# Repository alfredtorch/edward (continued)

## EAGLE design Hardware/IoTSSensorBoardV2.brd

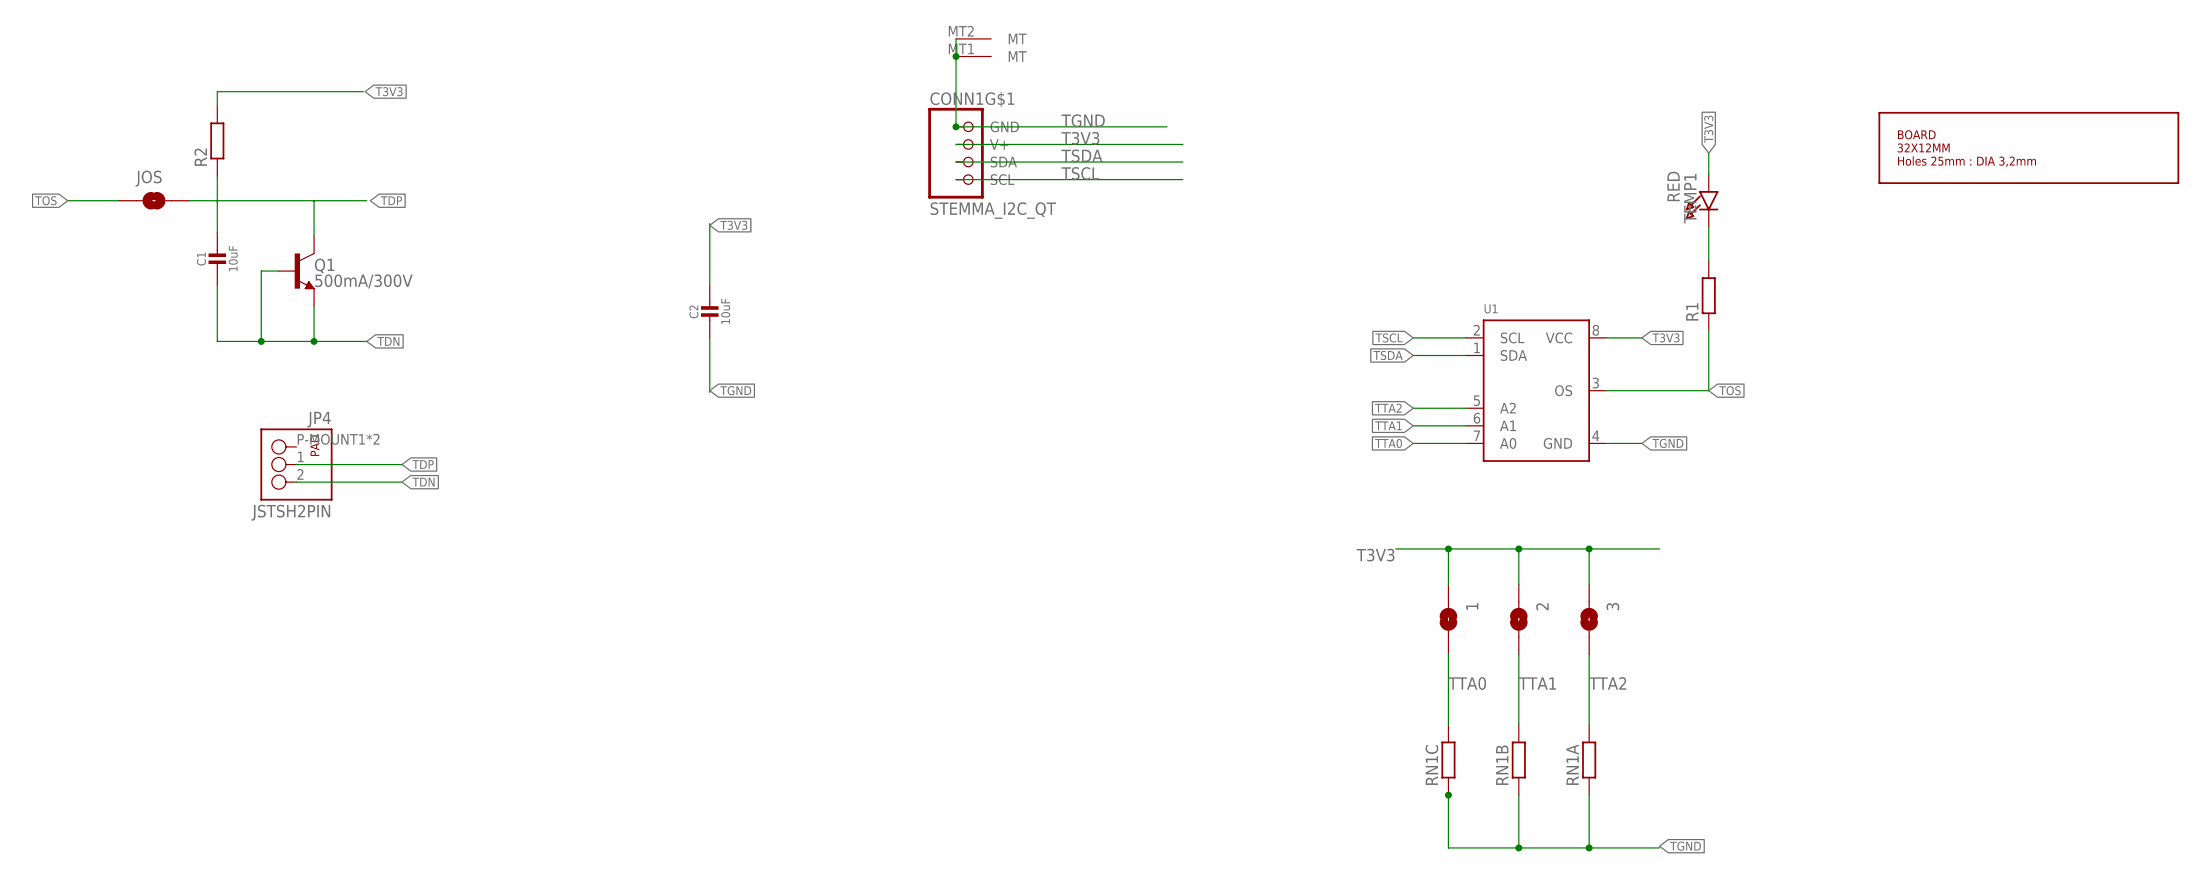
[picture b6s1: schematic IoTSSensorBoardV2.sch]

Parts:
1, 2, 3: JUMPER-SMT_2_NO_SILK; SMT-JUMPER_2_NO_SILK
C1, C2: 10uF; 0805-NO
CONN1: STEMMA_I2C_QT; JST_SH4
JOS: JUMPER-SMT_2_NO_SILK; SMT-JUMPER_2_NO_SILK
JP4: JSTSH2PIN; SM02B-SRSS-TB
Q1: 500mA/300V; SOT23-3
R1, R2: RESISTORR805-0805; R805
RN1: RESISTOR_ARRAY_4; RN8P-4R-CRA06S
TEMP1: RED; CHIPLED_0805
U1: TEMP_LM75B; TSSOP8
U$12: BOARD32X12; OVAL3212MM

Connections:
unnamed: R1.2, TEMP1.C
T3V3: 1.1, 2.1, 3.1, C2.1, CONN1.2 (V+), R2.2, TEMP1.A, U1.8 (VCC)
TDN: C1.2, JP4.2, Q1.1 (B), Q1.2 (E)
TDP: C1.1, JOS.2, JP4.1, Q1.3 (C), R2.1
TGND: C2.2, CONN1.1 (GND), CONN1.MT1 (MT), CONN1.MT2 (MT), RN1.1, RN1.2 (1), RN1.3 (1), U1.4 (GND)
TOS: JOS.1, R1.1, U1.3 (OS)
TSCL: CONN1.4 (SCL), U1.2 (SCL)
TSDA: CONN1.3 (SDA), U1.1 (SDA)
TTA0: 1.2, RN1.6 (2), U1.7 (A0)
TTA1: 2.2, RN1.7 (2), U1.6 (A1)
TTA2: 3.2, RN1.8 (2), U1.5 (A2)

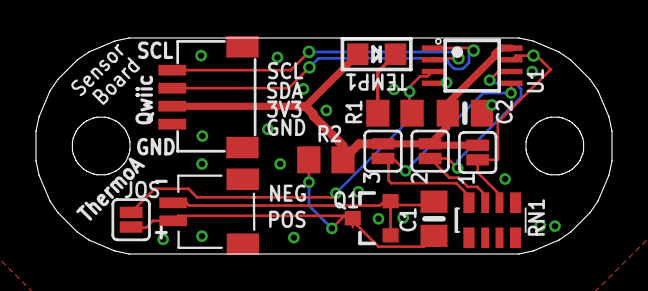
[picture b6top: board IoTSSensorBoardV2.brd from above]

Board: 2 copper layers, 32.0 x 12.0 mm, 15 parts (0 on the bottom side), 11 nets.

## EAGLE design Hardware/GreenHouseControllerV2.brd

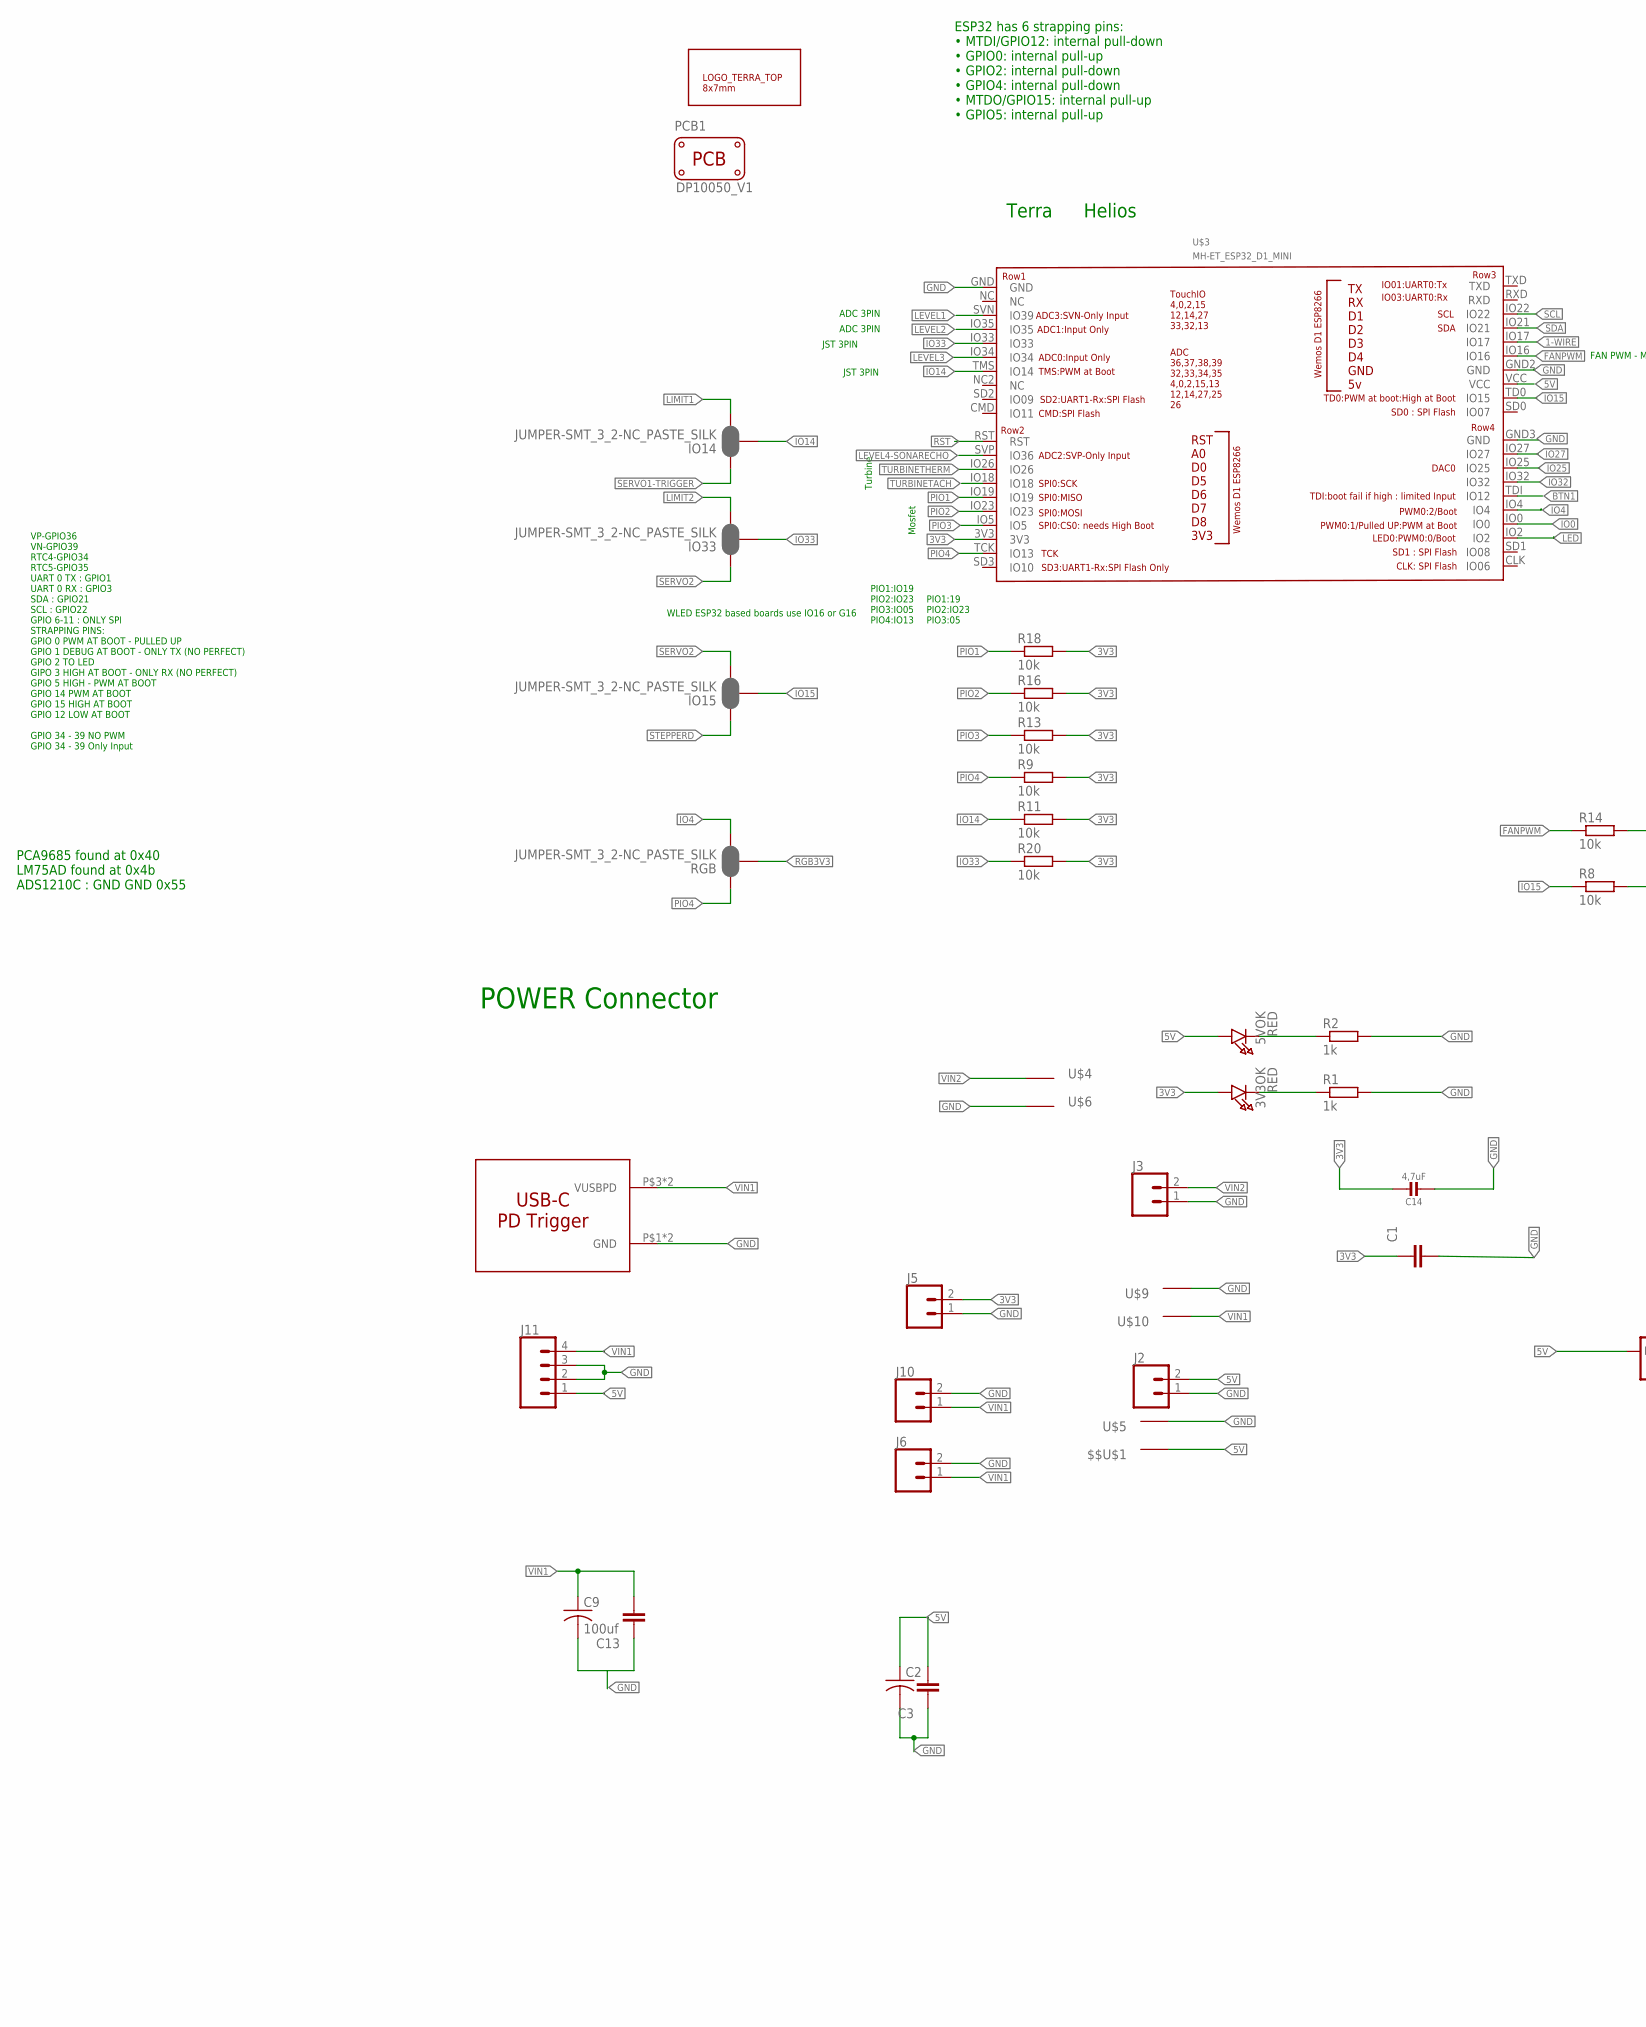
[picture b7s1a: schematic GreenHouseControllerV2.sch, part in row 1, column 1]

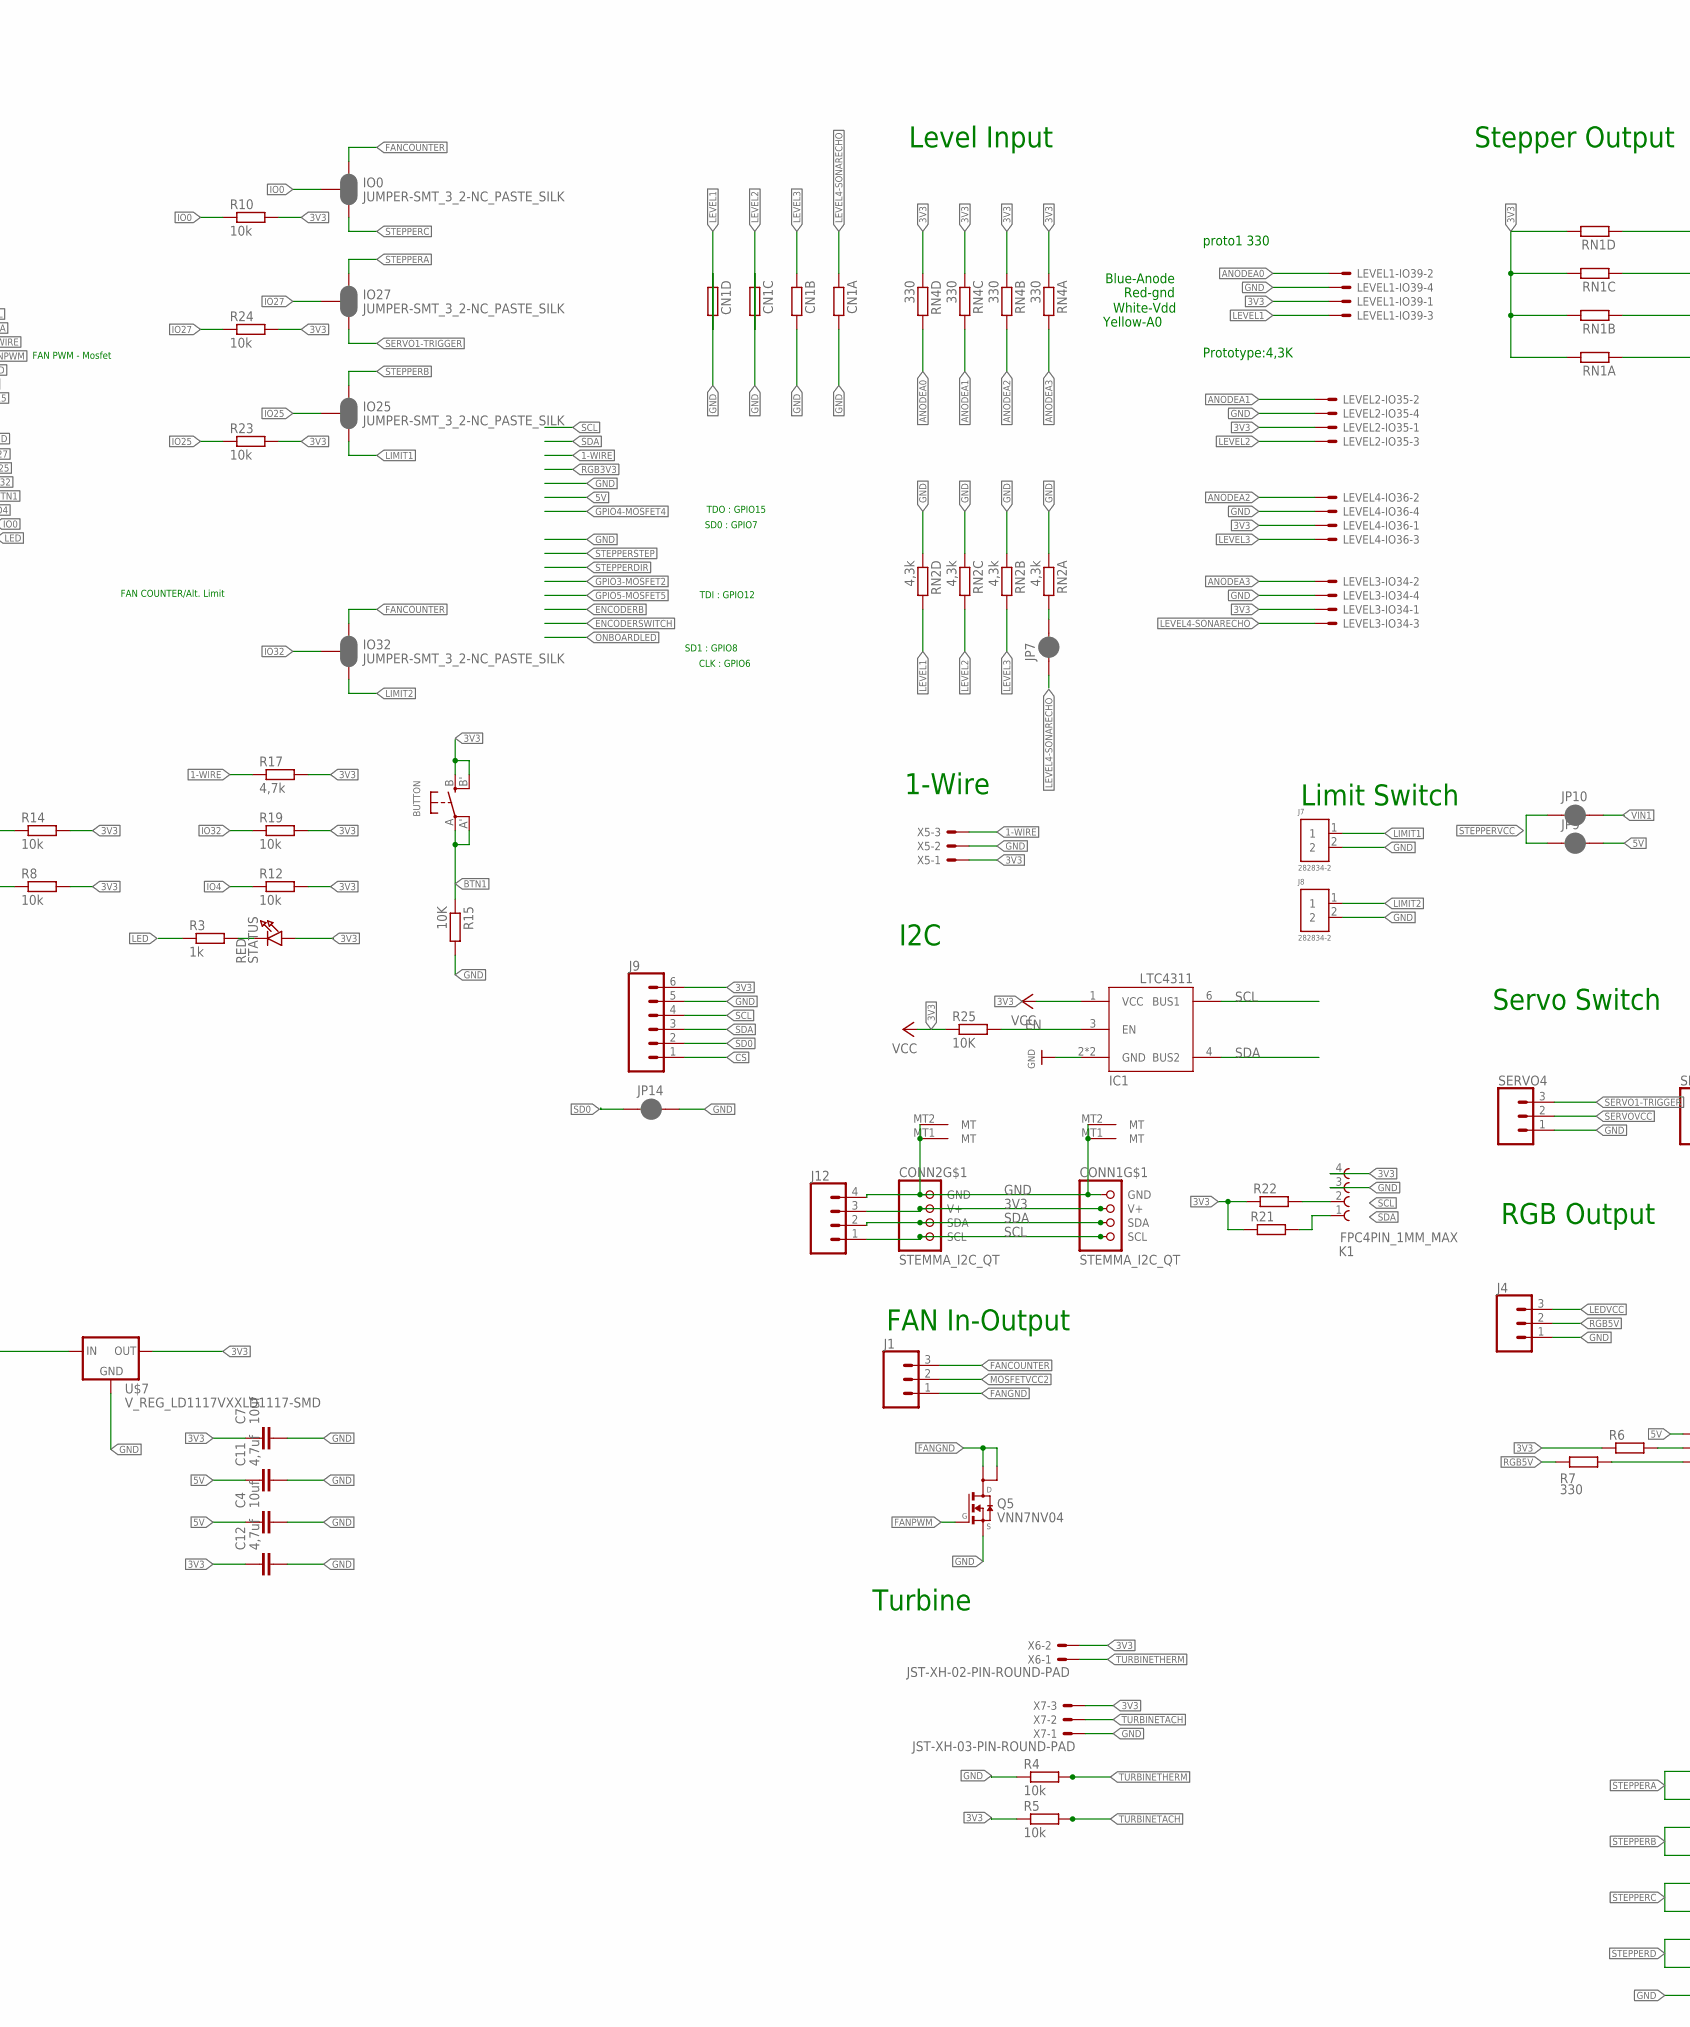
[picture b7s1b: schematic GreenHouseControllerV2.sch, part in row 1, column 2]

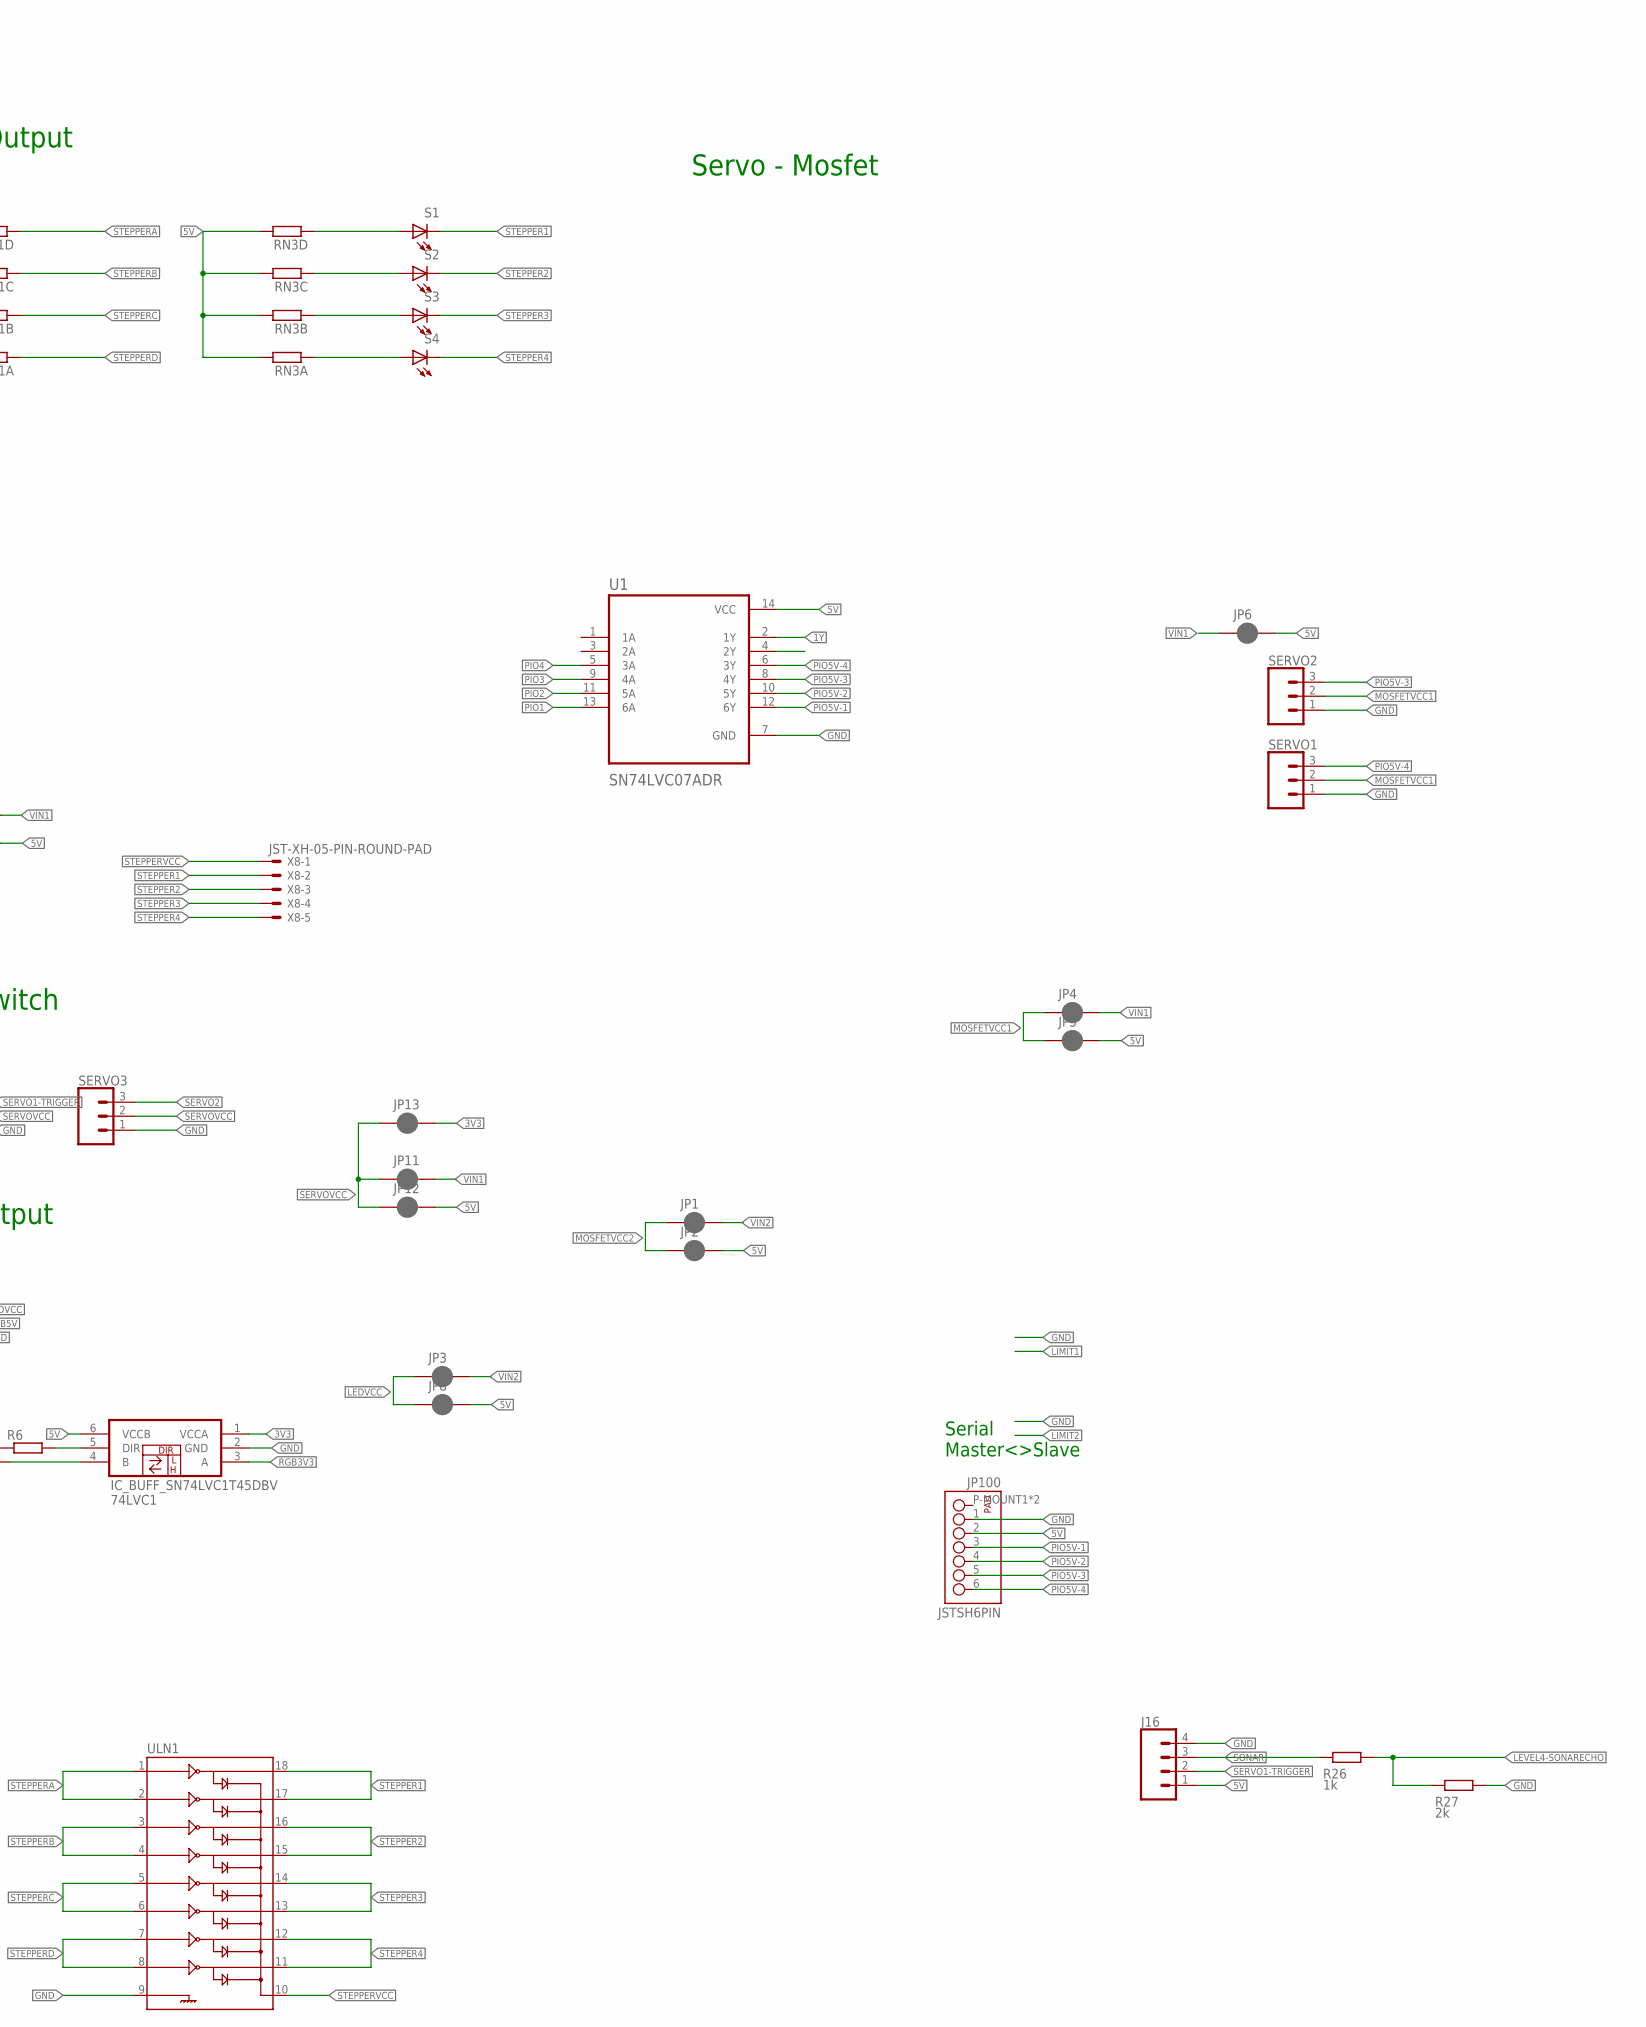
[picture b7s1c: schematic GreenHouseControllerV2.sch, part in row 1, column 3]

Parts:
3V3OK, 5VOK: RED; CHIPLED_0805
74LVC1: IC_BUFF_SN74LVC1T45DBV; DBV-R-PDSO-G6
$$U$1: TESTHOOK
BUTTON: KMR2; BTN_KMR2_4.6X2.8
C1, C3, C13: CAPACITOR_NPOL-0805; C805
C2: C-USC1210; C1210
C4, C7: 10uf; C805
C9: 100uf; C1210
C11, C12: 4,7uf; C805
C14: 4,7uF; 0805-NO
CN1: RESISTOR_ARRAY_4; RN8P-4R-CRA06S
CONN1, CONN2: STEMMA_I2C_QT; JST_SH4
IC1: LTC4311_SC70; SC70-6L
IO0, IO14, IO15, IO25, IO27, IO32, IO33: JUMPER-SMT_3_2-NC_PASTE_SILK; SMT-JUMPER_3_2-NC_PASTE_SILK
J1: CONN_03POLAR; MOLEX-1X3
J2, J3, J5: CONN_02POLAR; MOLEX-1X2
J4: CONN_03SCREW; SCREWTERMINAL-3.5MM-3
J6, J10: CONN_023.5MM; SCREWTERMINAL-3.5MM-2
J7, J8: 282834-2; CONN_282834-2
J9: CONN_06NO_SILK_FEMALE_PTH; 1X06_NO_SILK
J11: CONN_04; 1X04
J12: CONN_04JST-PH-4-1.0MM; JST-4-SMD-VERT-1.0MM
J16: CONN_04POLAR; MOLEX-1X4
JP1, JP2, JP3, JP4, JP5, JP6, JP7, JP8, JP9, JP10, JP11, JP12, JP13, JP14: JUMPER-SMT_2_NC_PASTE_SILK; SMT-JUMPER_2_NC_PASTE_SILK
JP100: JSTSH6PIN; SM06B-SRSS-TB
K1: FPC4PIN_1MM_MAX; FPC_CONN_DOC_4PIN_ENLARGED
LEVEL1-IO39, LEVEL2-IO35, LEVEL3-IO34, LEVEL4-IO36: JST-XH-04-PIN-ROUND-PAD; JST-XH-04-PACKAGE-ROUND-PAD
PCB1: PCB_DP_RECTANGLE-50X100; DP10050_V1
Q5: VNN7NV04; SOT223
R1, R2, R3, R26: 1k; R805
R4, R5, R8, R9, R10, R11, R12, R13, R14, R16, R18, R19, R20, R23, R24: 10k; R805
R6, R21, R22: RESISTORR805-0805; R805
R7: 330; R805
R15, R25: 10K; R805
R17: 4,7k; R805
R27: 2k; R805
RGB: JUMPER-SMT_3_2-NC_PASTE_SILK; SMT-JUMPER_3_2-NC_PASTE_SILK
RN1, RN3: RESISTOR_ARRAY_4; RN8P-4R-CRA06S
RN2: 4,3k; RN8P-4R-CRA06S
RN4: 330; RN8P-4R-CRA06S
S1, S2, S3, S4: LED-0805; LED-805
SERVO1, SERVO2, SERVO3, SERVO4: CONN_03POLAR; MOLEX-1X3
STATUS: RED; CHIPLED_0805
U1: SN74LVC07ADR; SOIC127P600X175-14N
U$1: LOGOTOPTERRA
U$3: MH-ET_ESP32_D1_MINI
U$4, U$5, U$6, U$9, U$10: TESTHOOK
U$7: V_REG_LD1117VXXLD1117-SMD; SOT223
U$8: USB_PD_TRIGGER; USB-PDTRIGGER
ULN1: ULN2803SOICW; SO18L
X5, X7: JST-XH-03-PIN-ROUND-PAD; JST-XH-03-PACKAGE-ROUND-PAD
X6: JST-XH-02-PIN-ROUND-PAD; JST-XH-02-PACKAGE-ROUND-PAD
X8: JST-XH-05-PIN-ROUND-PAD; JST-XH-05-PACKAGE-ROUND-PAD

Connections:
1-WIRE: R17.1, U$3.IO17, X5.3
1Y: U1.2 (1Y)
3V3: 3V3OK.A, 74LVC1.1 (VCCA), BUTTON.B (S), BUTTON.B' (S1), C1.1, C7.1, C12.1, C14.1, CONN1.2 (V+), CONN2.2 (V+), IC1.1 (VCC), J5.2, J9.6, J12.3, JP13.2, K1.4, LEVEL1-IO39.1, LEVEL2-IO35.1, LEVEL3-IO34.1, LEVEL4-IO36.1, R5.1, R6.1, R8.2, R9.2, R10.2, R11.2, R12.2, R13.2, R14.2, R16.2, R17.2, R18.2, R19.2, R20.2, R21.1, R22.1, R23.2, R24.2, R25.1, RN1.5 (2), RN1.6 (2), RN1.7 (2), RN1.8 (2), RN4.1, RN4.2 (1), RN4.3 (1), RN4.4 (1), STATUS.A, U$3.3V3, U$7.2 (OUT), X5.1, X6.2, X7.3
5V: 5VOK.A, 74LVC1.6 (VCCB), $$U$1.P$1, C2.1, C3.2, C4.1, C11.1, J2.2, J11.1, J16.1, JP2.2, JP5.2, JP6.2, JP8.2, JP9.2, JP12.2, JP100.2, RN3.5 (2), RN3.6 (2), RN3.7 (2), RN3.8 (2), U1.14 (VCC), U$3.VCC, U$7.3 (IN)
ANODEA0: LEVEL1-IO39.2, RN4.5 (2)
ANODEA1: LEVEL2-IO35.2, RN4.6 (2)
ANODEA2: LEVEL4-IO36.2, RN4.7 (2)
ANODEA3: LEVEL3-IO34.2, RN4.8 (2)
BTN1: BUTTON.A, BUTTON.A' (P1), R15.1, U$3.TDI (IO12)
CS: J9.1
EN: IC1.3 (EN), R25.2
FANCOUNTER: IO0.1, IO32.1, J1.3
FANGND: J1.1, Q5.2 (D), Q5.4 (D2)
FANPWM: Q5.1 (G), R14.1, U$3.IO16
GND: 74LVC1.2 (GND), C1.2, C2.2, C3.1, C4.2, C7.2, C9.2, C11.2, C12.2, C13.1, C14.2, CN1.3 (1), CN1.4 (1), CN1.7 (2), CN1.8 (2), CONN1.1 (GND), CONN1.MT1 (MT), CONN1.MT2 (MT), CONN2.1 (GND), CONN2.MT1 (MT), CONN2.MT2 (MT), IC1.2 (GND), IC1.5 (GND), J2.1, J3.1, J4.1, J5.1, J6.2, J7.2, J8.2, J9.5, J10.2, J11.2, J11.3, J12.4, J16.4, JP14.2, JP100.1, K1.3, LEVEL1-IO39.4, LEVEL2-IO35.4, LEVEL3-IO34.4, LEVEL4-IO36.4, Q5.3 (S), R1.2, R2.2, R4.1, R15.2, R27.2, RN2.1, RN2.2 (1), RN2.3 (1), RN2.4 (1), SERVO1.1, SERVO2.1, SERVO3.1, SERVO4.1, U1.7 (GND), U$3.GND, U$3.GND2 (GND), U$3.GND3 (GND), U$5.P$1, U$6.P$1, U$7.1 (GND), U$8.P$1 (GND), U$8.P$2 (GND), U$9.P$1, ULN1.9, X5.2, X7.1
IO0: IO0.2, R10.1, U$3.IO0
IO4: R12.1, RGB.3, U$3.IO4
IO14: IO14.2, R11.1, U$3.TMS (IO14)
IO15: IO15.2, R8.1, U$3.TD0 (IO15)
IO25: IO25.2, R23.1, U$3.IO25
IO27: IO27.2, R24.1, U$3.IO27
IO32: IO32.2, R19.1, U$3.IO32
IO33: IO33.2, R20.1, U$3.IO33
LED: R3.1, U$3.IO2
LEDVCC: J4.3, JP3.1, JP8.1
LEVEL1: CN1.5 (2), LEVEL1-IO39.3, RN2.5 (2), U$3.SVN (IO39)
LEVEL2: CN1.6 (2), LEVEL2-IO35.3, RN2.6 (2), U$3.IO35
LEVEL3: CN1.2 (1), LEVEL4-IO36.3, RN2.7 (2), U$3.IO34
LEVEL4-SONARECHO: CN1.1, JP7.1, LEVEL3-IO34.3, R26.2, R27.1, U$3.SVP (IO36)
LIMIT1: IO14.3, IO25.3, J7.1
LIMIT2: IO32.3, IO33.3, J8.1
MOSFETVCC1: JP4.1, JP5.1, SERVO1.2, SERVO2.2
MOSFETVCC2: J1.2, JP1.1, JP2.1
unnamed: 5VOK.C, R2.1
unnamed: R3.2, STATUS.C
unnamed: JP7.2, RN2.8 (2)
unnamed: 3V3OK.C, R1.1
unnamed: RN3.4 (1), S1.A
unnamed: RN3.3 (1), S2.A
unnamed: RN3.2 (1), S3.A
unnamed: RN3.1, S4.A
unnamed: 74LVC1.5 (DIR), R6.2
unnamed: 74LVC1.4 (B), R7.2
PIO1: R18.1, U1.13 (6A), U$3.IO19
PIO2: R16.1, U1.11 (5A), U$3.IO23
PIO3: R13.1, U1.9 (4A), U$3.IO5
PIO4: R9.1, RGB.1, U1.5 (3A), U$3.TCK (IO13)
PIO5V-1: JP100.3, U1.12 (6Y)
PIO5V-2: JP100.4, U1.10 (5Y)
PIO5V-3: JP100.5, SERVO2.3, U1.8 (4Y)
PIO5V-4: JP100.6, SERVO1.3, U1.6 (3Y)
RGB3V3: 74LVC1.3 (A), RGB.2
RGB5V: J4.2, R7.1
RST: U$3.RST
SCL: CONN1.4 (SCL), CONN2.4 (SCL), IC1.6 (BUS1), J9.4, J12.1, K1.2, R22.2, U$3.IO22
SD0: J9.2, JP14.1
SDA: CONN1.3 (SDA), CONN2.3 (SDA), IC1.4 (BUS2), J9.3, J12.2, K1.1, R21.2, U$3.IO21
SERVO1-TRIGGER: IO14.1, IO27.3, J16.2, SERVO4.3
SERVO2: IO15.3, IO33.1, SERVO3.3
SERVOVCC: JP11.1, JP12.1, JP13.1, SERVO3.2, SERVO4.2
SONAR: J16.3, R26.1
STEPPER1: S1.C, ULN1.17, ULN1.18, X8.2
STEPPER2: S2.C, ULN1.15, ULN1.16, X8.3
STEPPER3: S3.C, ULN1.13, ULN1.14, X8.4
STEPPER4: S4.C, ULN1.11, ULN1.12, X8.5
STEPPERA: IO27.1, RN1.4 (1), ULN1.1, ULN1.2
STEPPERB: IO25.1, RN1.3 (1), ULN1.3, ULN1.4
STEPPERC: IO0.3, RN1.2 (1), ULN1.5, ULN1.6
STEPPERD: IO15.1, RN1.1, ULN1.7, ULN1.8
STEPPERVCC: JP9.1, JP10.1, ULN1.10, X8.1
TURBINETACH: R5.2, U$3.IO18, X7.2
TURBINETHERM: R4.2, U$3.IO26, X6.1
VIN1: C9.1, C13.2, J6.1, J10.1, J11.4, JP4.2, JP6.1, JP10.2, JP11.2, U$8.P$3 (VUSBPD), U$8.P$4 (VUSBPD), U$10.P$1
VIN2: J3.2, JP1.2, JP3.2, U$4.P$1

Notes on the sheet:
PCA9685 found at 0x40 LM75AD found at 0x4b ADS1210C : GND GND 0x55
Blue-Anode
Red-gnd
White-Vdd
Yellow-A0
Prototype:4,3K
proto1 330
VP-GPIO36 VN-GPIO39 RTC4-GPIO34 RTC5-GPIO35 UART 0 TX : GPIO1 UART 0 RX : GPIO3 SDA : GPIO21 SCL : GPIO22 GPIO 6-11 : ONLY SPI STRAPPING PINS: GPIO 0 PWM AT BOOT - PULLED UP GPIO 1 DEBUG AT BOOT - ONLY TX (NO PERFECT) GPIO 2 TO LED GIPO 3 HIGH AT BOOT - ONLY RX (NO PERFECT) GPIO 5 HIGH - PWM AT BOO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
SD1 : GPIO8
CLK : GPIO6
SD0 : GPIO7
TDO : GPIO15
WLED ESP32 based boards use IO16 or G16
TDI : GPIO12
Terra
Helios
Mosfet
Turbine
ADC 3PIN
JST 3PIN
FAN PWM - Mosfet
FAN COUNTER/Alt. Limit
Level Input
RGB Output
Stepper Output
I2C
POWER Connector
Servo - Mosfet
FAN In-Output
Limit Switch
Servo Switch
1-Wire
ESP32 has 6 strapping pins: • MTDI/GPIO12: internal pull-down • GPIO0: internal pull-up • GPIO2: internal pull-down • GPIO4: internal pull-down • MTDO/GPIO15: internal pull-up • GPIO5: internal pull-up
Serial Master<>Slave
PIO1:19 PIO2:IO23 PIO3:05
PIO1:IO19 PIO2:IO23 PIO3:IO05 PIO4:IO13

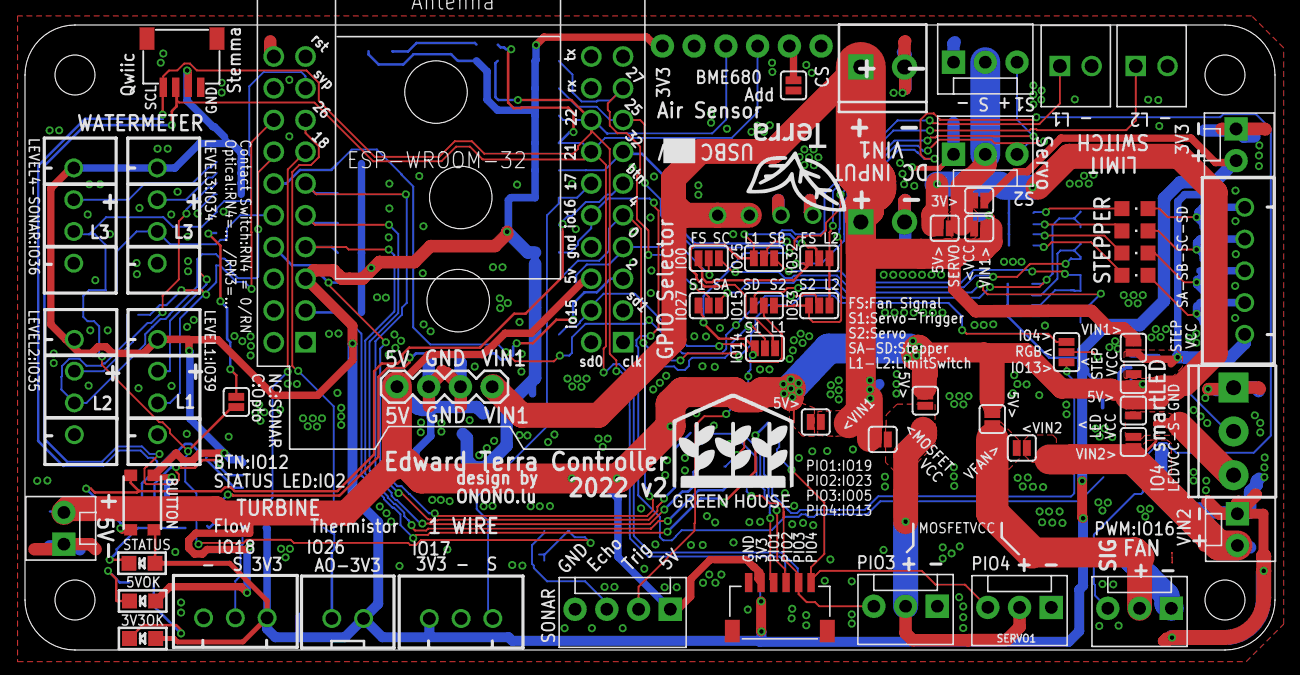
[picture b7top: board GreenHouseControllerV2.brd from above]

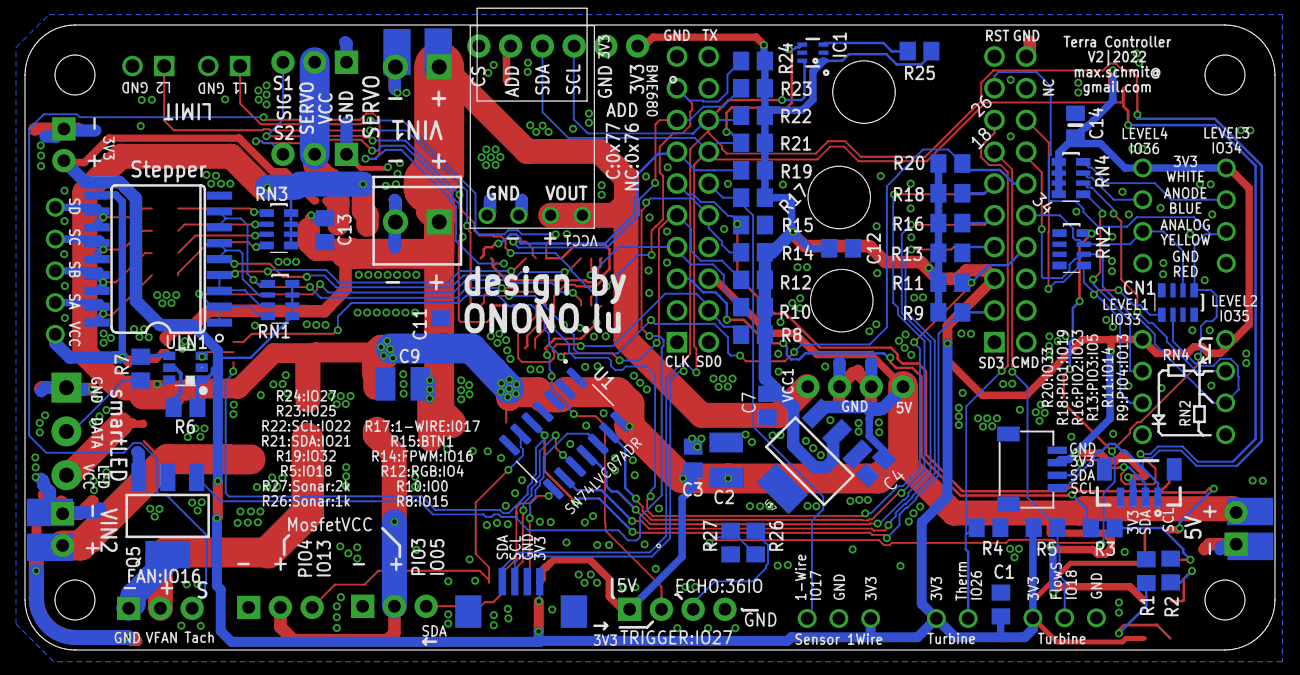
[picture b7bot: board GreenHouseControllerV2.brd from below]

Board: 2 copper layers, 100.0 x 50.0 mm, 118 parts (59 on the bottom side), 71 nets.

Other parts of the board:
U$2: LOGOGREENHOUSE

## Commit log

2023-11-04 Create home-assistant
